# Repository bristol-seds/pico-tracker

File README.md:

bristol-seds.github.io/pico-tracker
======================
Available at http://bristol-seds.github.io/pico-tracker.

## Running the server for local testing

You need Jekyll installed:

    $ sudo gem install jekyll RedCloth

Start Jekyll:

    $ jekyll serve --watch

Note that changes to `_config.yml` may require restarting the server.

#Items from the main site, may not work here:

## Adding photo carousels

First put all photos in the `asset_path` directory for a post. Then list all in the front-matter like so:

    photos:
      - url: photo1.jpg
      - url: photo2.jpg
      - url: photo3.jpg

Then simply add {% raw %}`{% include carousel.html %}`{% raw %} where you want the carousel.

## Adding Javascript to posts

Make sure your post has an `asset_path` key-value pair.

### Google Maps

Add a new key, `maps:`, with a list of `url:` key-value pairs as its value, each having
a script containing a Google Maps generator as its value, e.g.:

    maps:
      - url: map1.js
      - url: map2.js

The scripts should be placed in the `asset_path` directory.
For each map, insert a `<div>` tag into the post, with a unique ID referenced by the map generator script.
**TO-DO**: Google Maps KML files must be hosted publicly. Find a way to automatically insert the KML file's fully-qualified url into a map script. Currently I'm just hosting them from http://samhatfield.co.uk

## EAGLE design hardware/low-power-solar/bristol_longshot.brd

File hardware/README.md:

#### Hardware Revisions

Most hardware that has been built has a version number

|Version|Description|Exists/Existed|Flights used on
|----|----|----|----
|v0.96.0|Original AAA Battery. Flown with modifications to connect tcxo to mcu.|x|UBSEDS3-8?+UBSEDS12
|v0.981.0|Solar Power SPV1040. Flown with modifications simplify power circuit.|x|UBSEDS9
|v0.981.1|Minor fixes|
|v0.982.0|AAA Battery. Never fully populated, used for lab testing.|x|
|v0.982.1|Minor fixes|
|v0.984.0|First attempt at internal balloon board|
|v0.985.0|Solar Power/Primary AAA Lithium|x|UBSEDS10-11
|v0.985.1|Added DNP/0Ω between solar and MPPT set for use when only a battery is connected|
|v0.985.2|BMP180 -> MS5607 Pressure / Temperature Sensor|
|v0.985.3|Smaller holes for external thermistor|
|v0.986.0|Low Power with side mounting GPS chip antenna|
|v0.986.1|Low Power. Add 10k i2c pull ups|
|v0.986.1|Low Power. Rearranged matching network|
|v0.986.3|Low Power. Added L0'-C0' tank in paralell. Might work, should test|
|v0.986.4|Low Power. Added LIS2D accelerometer. Optional|
|v0.986.5|Low Power. Added TS3006 low power lf clock|
|v0.986.6|Low Power. Added LDO for GPS, LF TCXO for GPS|
|v0.986.7|Low Power. Changed low power lf clock, added vreg on breakout for optional power testing|
|v0.986.8|Low Power. Changed memory pads, GPS LDO and specified SAMD20E18A-MN with more flash and higher grade packaging|x|
|v0.986.9|Low Power. 80x80mm Breakout|
|v0.987.0|Low Power. Added 32kHz TCXO RC filters, replaced GPS LDO with MOSFET, remove IMU, vreg on b/out, update SE880 footprint, Watchdog, Radio, filter design
|v0.987.1|Low Power. Switch LF Clock to XOSC32K pin from GCLK_IO[0]. Allows feed to any GCLK. Bit-bang i2c instead|
|v0.987.2|Low Power. Adjusted 100µF cap from 1210 to 1206|x|
|v0.987.3|Low Power. Added pull-down on WDI

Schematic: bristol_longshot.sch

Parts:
A1: 1575AT43A40
C0, C2: 15pF; _0402
C1, C3: 8.2pF; _0402
C4, C48: DNP; _0402
C5: 5.1pF; _0402
C6: 2.7pF; _0402
C7, C13, C14, C15, C16, C17, C18, C20, C21, C34, C46, C47, C49, C51: 100nF; _0402
C8, C9, C10: 100pF; _0402
C11, C30: 4.7µF; _0402
C12, C39, C40, C41, C42, C44, C45: 10nF; _0402
C19: 18nF; _0402
C22, C27, C33: 10µF; C0603K
C23, C24, C26, C35, C52: 1µF; _0402
C25, C28: 2.2µF; _0402
C29, C32: 100µF; C1206K
C31: 47nF; _0402
C36, C37: 56pF; _0402
C38: 39pF; _0402
C43: 27pF; _0402
C50: 10nF; _0805
D1, D2, D3, D4, D5: RB161M
D6: MBR0520LT1G; SOD123W
DZ1: 5V6, 500mW; SOD-323
FB1, FB2: FERRITE_0402; _0402
FB3: FERRITE_0603; _0603
JP1: BATTERY_TERMINAL; 1X02_LOCK
JP2: SOLAR_TERMINAL; 1X02_LOCK
JP3: M02LOCK; 1X02_LOCK
JTAG1: JTAG-CORTEXM3SMT; 2X05_1.27MM_SMT
L0, L6, L7: 56nH; _0402@2
L1: XFL4030-4.7µH; XFL4020
L2: 2.2µH; 1007
L3: 110nH; _0805MP
L4, L5, L11: 18nH; _0402@2
L8: EPL2010-680nH; EPL2010
L9, L10: 33nH; _0603MP
L12: 0Ω; _0402@2
LC: 470nH; _0402@2
LED1, LED2: GREEN; CHIPLED_0603
Q1, Q2: NX2301P; SOT23
Q3, Q4: BSS84; SOT23
Q5: PBSS4130; SOT1118
Q6: PD84001; SOT-89
R1, R2, R3, R4, R7, R8, R24, R27, R29, R30, R33: 10kΩ; _0402
R5: 20kΩ; _0402
R6, R9, R10, R11, R12, R13: 100kΩ; _0402
R14: 75kΩ; _0402
R15, R16, R17: 1MΩ; _0402
R18: 4.7kΩ; _0402
R19, R22, R31, R32: 1kΩ; _0402
R20, R21: 22Ω; _0603MP
R23: 4.7Ω; _0402
R25, R26: 33kΩ; _0402
R28: 330Ω; _0402
U1: SAM_D20E; QFN32_5MM
U2: SI4461; QFN20
U3: SE880
U4: SST25WF040BT-40I/NP; USON-8
U5: TG-5006CJ; TC-5006CJ
U6: TPS73118DBVT; SOT95P280X145-5N
U7: ADM6823WYRJZ; SOT23-5
U8: SN74LVC1G32DCKR; SOT65P210X110-5N
U9: TPS62243; S-PWSON-N6
U10, U11: SIT1552
U12: LTC4070EMS8EPBF; SOP65P490X110-9N
U13: ADP1614ACPZ-1.3-R7; DFN50P300X300X80-11N
U14, U15: TPS71533DCKR; SOT65P210X110-5N
U16, U17, U18: 74LVC1G04GW; SOT65P210X110-5N
U19: AS213-92; SOT-6
U20: SKY13373

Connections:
1.8V: C10.1, C15.1, C17.1, C21.1, C32.1, C33.1, FB1.2, FB2.2, FB3.2, JTAG1.1, L2.2, LED1.A, R4.2, R12.2, R31.2, R32.2, U1.9 (VDD_ANA), U1.30 (VDD), U4.7 (!HOLD), U4.8 (VDD), U7.3 (!MR), U7.5 (VDD), U8.5 (VCC), U9.3 (FB), U10.3 (VCC), U17.5 (VCC), U18.5 (VCC)
1.8V_EN: JP3.1, R30.2, U9.4 (EN)
2M_FILTER_1: C36.1, C39.2, L9.1
2M_FILTER_2: C37.1, L9.2, L10.1
2M_FILTER_3: C38.1, C45.1, L10.2
7.5V: C27.1, C29.1, C51.1, D6.P$2 (2), L3.2, R9.2, U14.4 (IN)
!GPS_EN: Q1.1 (G), R15.1, U1.2 (PA01)
!RESET: U1.26 (RESETN), U8.4 (Y)
AMPL_DRAIN: C39.1, L3.1, Q6.3 (D)
AMPL_GATE: L11.2, Q6.1 (G), R19.1
AMPL_IN: C41.2, C43.1, L11.1
AMPL_IN1: C41.1, U19.3 (J2)
AMPL_OUT: C45.2, U20.1 (J1)
ANT: C48.1, L12.2
ANT1: C4.1, C40.2, L12.1
BATTERY: C22.1, D3.ANODE (A), JP1.1, Q4.3 (D), R23.2, R25.2, U12.2 (NTC), U12.8 (VCC)
BATTERY_MOSFET_1: Q3.3 (D), Q4.2 (S)
BATTERY_SENSE: R24.2, R25.1, U1.5 (PA04)
BOOST_COMP: R18.2, U13.1 (COMP)
BOOST_COMP_1: C19.1, R18.1
BOOST_CURRENTLIMIT: R14.2, U13.9 (CLRES)
BOOST_FB: R5.2, R9.1, U13.2 (FB)
BOOST_SOFTSTART: C31.1, U13.10 (SS)
BOOST_SUPPLY: C30.1, L1.1, Q2.3 (D), U13.3 (EN), U13.8 (VIN)
BOOST_SUPPLY_CTRL_B: Q5.P2 (B), R29.2
BOOST_SUPPLY_CTRL_C: Q2.1 (G), Q5.P3 (C), Q5.P8 (C), R10.2
BOOST_SW: D6.P$1 (1), L1.2, U13.6 (SW_2), U13.7 (SW)
BUCK_SW: L2.1, U9.1 (SW)
BYPASS: C42.2, U20.3 (J3)
BYPASS1: C42.1, U19.1 (J3)
CHG_CTRL: R33.1, U1.25 (PA27)
CHG_CTRL_B: Q5.P5 (B), R33.2
CHG_CTRL_C: Q3.1 (G), Q4.1 (G), Q5.P6 (C), Q5.P7 (C), R6.2
CHG_LED: LED2.A, R28.1
EXT!RESET: JTAG1.10, R1.2, U8.1 (A)
EXT_THERMISTOR_SENSE: R11.2, U1.3 (PA02)
FILTER1: C3.1, L0.1, L4.2
FILTER2: C2.1, L4.1, L5.2
GIMO: U1.7 (PA06), U3.34 (RX)
GND: C1.2, C2.2, C3.2, C4.2, C5.2, C7.2, C8.2, C9.2, C10.2, C11.2, C12.2, C15.2, C16.2, C17.2, C19.2, C20.2, C21.2, C22.2, C23.2, C24.2, C25.2, C26.2, C27.2, C28.2, C29.2, C30.2, C31.2, C32.2, C33.2, C34.2, C35.2, C36.2, C37.2, C38.2, C43.2, C46.1, C47.1, C48.2, C49.2, C51.2, C52.2, DZ1.A, JP1.2, JP2.2, JP3.2, JTAG1.3, JTAG1.5, LED2.C, Q5.P1 (E), Q5.P4 (E), Q6.2 (S), Q6.2.1 (S), R1.1, R2.1, R3.1, R5.1, R11.1, R13.1, R14.1, R16.1, R17.1, R22.1, R24.1, R27.1, U1.10 (GND1), U1.28 (GND2), U1.33 (GND), U2.5 (NC/GND), U2.18 (GND2), U2.PAD (GND), U3.1 (GND1), U3.5 (GND2), U3.18 (GND3), U3.20 (GND4), U3.23 (GND5), U3.24 (GND6), U3.25 (GND7), U3.26 (GND8), U3.28 (GND9), U3.29 (GND10), U4.4 (VSS), U5.2 (GND), U6.2 (GND), U7.2 (GND), U8.3 (GND), U9.2 (MODE), U9.6 (GND), U9.PAD (GND2), U10.1 (GND), U10.4 (GND1), U11.1 (GND), U11.4 (GND1), U12.3 (ADJ), U12.5 (GND), U12.9 (EP), U13.4 (GND_2), U13.5 (GND), U13.11 (EP), U14.2 (GND), U15.2 (GND), U16.3 (GND), U17.3 (GND), U18.3 (GND), U19.2 (GND), U20.2 (GND), U20.7 (GND1), U20.8 (GND2), U20.10 (GND3), U20.12 (GND4), U20.PAD
GOMI: U1.8 (PA07), U3.33 (TX)
GPS_ANT: A1.1 (ANT), U3.27 (RF_IN)
GPS_VDD: FB3.1, Q1.2 (S), R15.2
GPS_VDD_SWITCHED: C7.1, C9.1, C28.1, Q1.3 (D), U3.8 (VKA), U3.9 (VDD), U11.3 (VCC)
HBO: R28.2, U12.4 (HBO)
LED1: LED1.C, U1.16 (PA15)
LF_CLOCK: R7.1, U1.1 (PA00)
LF_CLOCK_OUT: R7.2, U10.2 (OUT)
LIION_CAP: C49.1, D4.CATHODE (C), D5.ANODE (A)
LIION_CAP_FEED: D4.ANODE (A), R23.1
MEM_CSN: U1.13 (PA10), U4.1 (!CE)
MEM_MISO: U1.14 (PA11), U4.2 (SO/SIO1)
MEM_MOSI: U1.11 (PA08), U4.5 (SI/SIO0)
MEM_SCK: U1.12 (PA09), U4.6 (SCK)
MEM_WPN: U4.3 (!WP)
NTCBIAS: U12.1 (NTCBIAS)
RADIO_VDD: C8.1, C20.1, C25.1, C34.1, FB1.1, LC.2, U2.6 (VDD), U2.8 (VDD2), U16.5 (VCC)
RADIO_XIN: C13.2, U2.17 (XIN)
RF_SW_V2: C47.2, U16.4 (Y), U19.6 (V2)
RF_TANK: C0.1, L0.2
RF_TCXO_REG_EN: U1.17 (PA16), U6.3 (EN)
RTC_XI: R8.1, U3.12 (RTC_XI)
RTC_XO: U3.13 (RTC_XO)
RX: C6.1, C50.1, L7.1
RXN: C5.1, L6.1, L7.2, U2.2 (RXP)
RXP: C6.2, L6.2, U2.3 (RXN)
RX_1: C50.2, U20.9 (J2)
SAM_XOSC: C18.1, R12.1, R13.2, U1.15 (PA14)
SE800_LF_OUT: R8.2, U11.2 (OUT)
SE_GPIO0: R2.2, U3.17 (GPIO0)
SE_GPIO1: R3.2, U3.16 (GPIO1)
SE_MODE_PULL: R4.1, U3.31 (CTS_SPI)
SE_ON_OFF: U1.6 (PA05), U3.3 (ON_OFF)
SE_TCXO_CLK: C14.1, U3.21 (TCXO_CLK)
SE_VBB: L8.1, U3.6 (VBB_I)
SE_VREG: L8.2, U3.7 (VREG_O)
SI_GPIO0: C46.2, R22.2, R29.1, U2.9 (GPIO0), U16.2 (A), U19.4 (V1)
SI_GPIO1: U1.24 (PA25), U2.10 (GPIO1)
SI_GPIO2: R31.1, U2.19 (GPIO2), U17.2 (A)
SI_GPIO3: R32.1, U2.20 (GPIO3), U18.2 (A)
SI_MISO: U1.21 (PA22), U2.13 (SDO)
SI_MOSI: U1.20 (PA19), U2.14 (SDI)
SI_NIRQ: U1.23 (PA24), U2.11 (NIRQ)
SI_NSEL: U1.19 (PA18), U2.15 (NSEL)
SI_SCLK: U1.22 (PA23), U2.12 (SCLK)
SI_SDN: U1.18 (PA17), U2.1 (SDN)
SI_TX: C0.2, LC.1, U2.4 (TX)
SKY_OUT: C40.1, U20.11 (RFC)
SKY_V1: R20.1, U20.4 (V1)
SKY_V1_1: R20.2, U17.4 (Y)
SKY_V2: R21.1, U20.5 (V2)
SKY_V2_1: R21.2, U18.4 (Y)
SOLAR1: D1.ANODE (A)
SOLAR2: D2.ANODE (A)
SWDCLK: JTAG1.4, U1.31 (PA30/SWCLK)
SWDIO: JTAG1.2, U1.32 (PA31/SWDIO)
TCXO_OUT: C13.1, C14.2, C18.2, U5.3 (OUT)
TCXO_REG_IN: C23.1, FB2.1, U6.1 (IN)
TCXO_REG_NR: C12.1, U6.4 (NR/FB)
TCXO_VDD: C24.1, U5.4 (VCC), U6.5 (OUT)
TIMEPULSE: U3.4 (TM)
TX: C1.1, C44.1, L5.1
TX_1: C44.2, U19.5 (J1)
VDD_CORE: C16.1, U1.29 (VDD_CORE)
V_BUS: C11.1, C52.1, D1.CATHODE (C), D2.CATHODE (C), D3.CATHODE (C), D5.CATHODE (C), DZ1.C, JP2.1, Q2.2 (S), Q3.2 (S), R6.1, R10.1, R26.2, R30.1, U9.5 (VIN), U15.4 (IN)
V_BUS_SENSE: R26.1, R27.2, U1.4 (PA03)
V_GG: C26.1, R19.2, U14.5 (OUT)
V_SKY: C35.1, U15.5 (OUT), U20.6 (VDD)
WDI: R17.2, U1.27 (PA28), U7.4 (WDI)
WDI!RESET: R16.2, U7.1 (!RESET), U8.2 (B)

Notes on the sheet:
ARM Cortex M0+: Atmel SAM D20E
(SERCOM3)
(SWD)
(EXTINT[12])
(DO: PAD3, SCK: PAD1)
(DOPO: 0x2)
(SERCOM2)
(DO: PAD0, SCK: PAD1, DOPO: 0x0)
(SERCOM0)
(TX: PAD2, TXPO: 0x1)
SST25WF04 4 MBit SPI Flash
Si4468 Transciever
Tuned for 434MHz
Radio
(0.8V p-p min)
(AIN[4])
Microcontroller
Set UART 115200 OSP
Set UART
(AIN[0])
SiT1552 Low frequency clock
Bypass Capacitors near SE880 main feed
Startup within 300ms
C15 in close proximity
MOSFET included to cycle GPS power as required
V_GSth = -1.1V @ Id = 0.1A
R_DSon = 0.2Ω @ V_GS = -1.8V, Id = 0.1A
approx. 20mV dropout
Input C < 15pF
Battery Voltage
Use ADM6823WYRJZ
Vth = 1.62-1.71V t_RP = 140-280ms t_WD = 1.12-2.4s
t_WD is 0.93x nominal at -40ºC
XOSC32K_IN
Icc = 5µA nominal at 1.8V
Icc = 10µA max
Pull-down to ensure watchdog bites if WDI left floating pre-init
Input Voltage: 2 - 6V
Enable: Vil = 0.4V, Vih=1V
Undervoltage Lockout: 1.85V typ

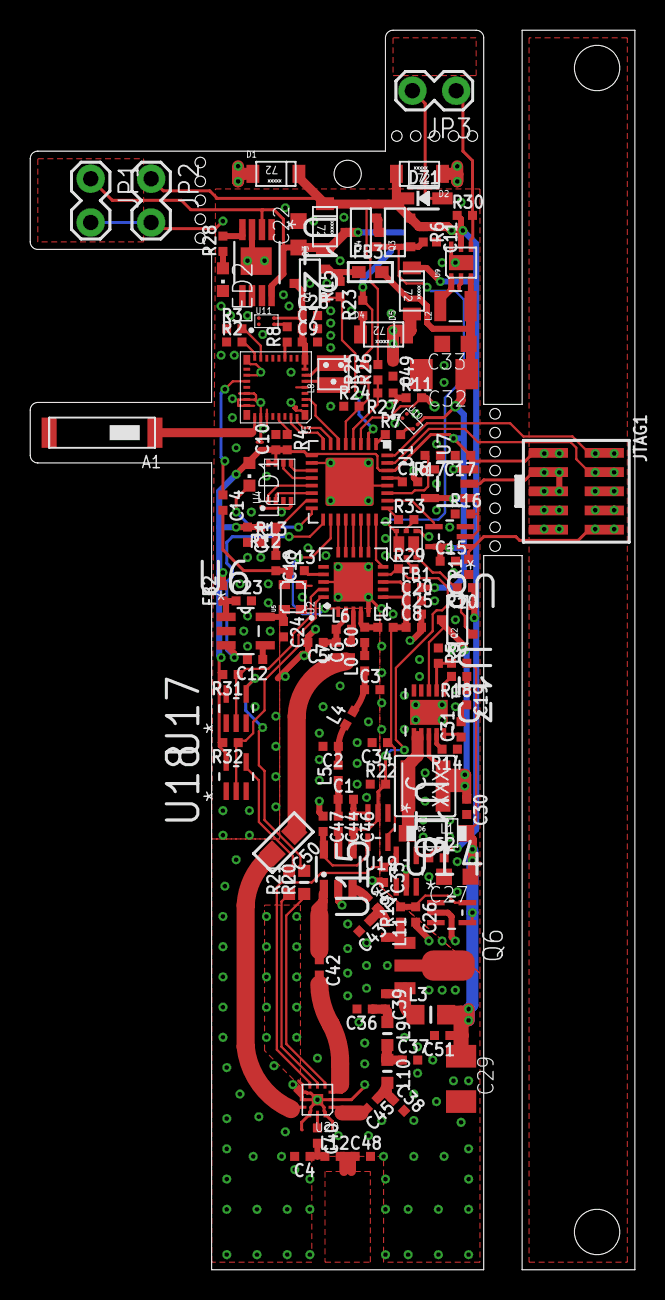
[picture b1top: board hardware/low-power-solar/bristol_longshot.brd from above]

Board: 2 copper layers, 40.0 x 82.0 mm, 143 parts (0 on the bottom side), 104 nets.

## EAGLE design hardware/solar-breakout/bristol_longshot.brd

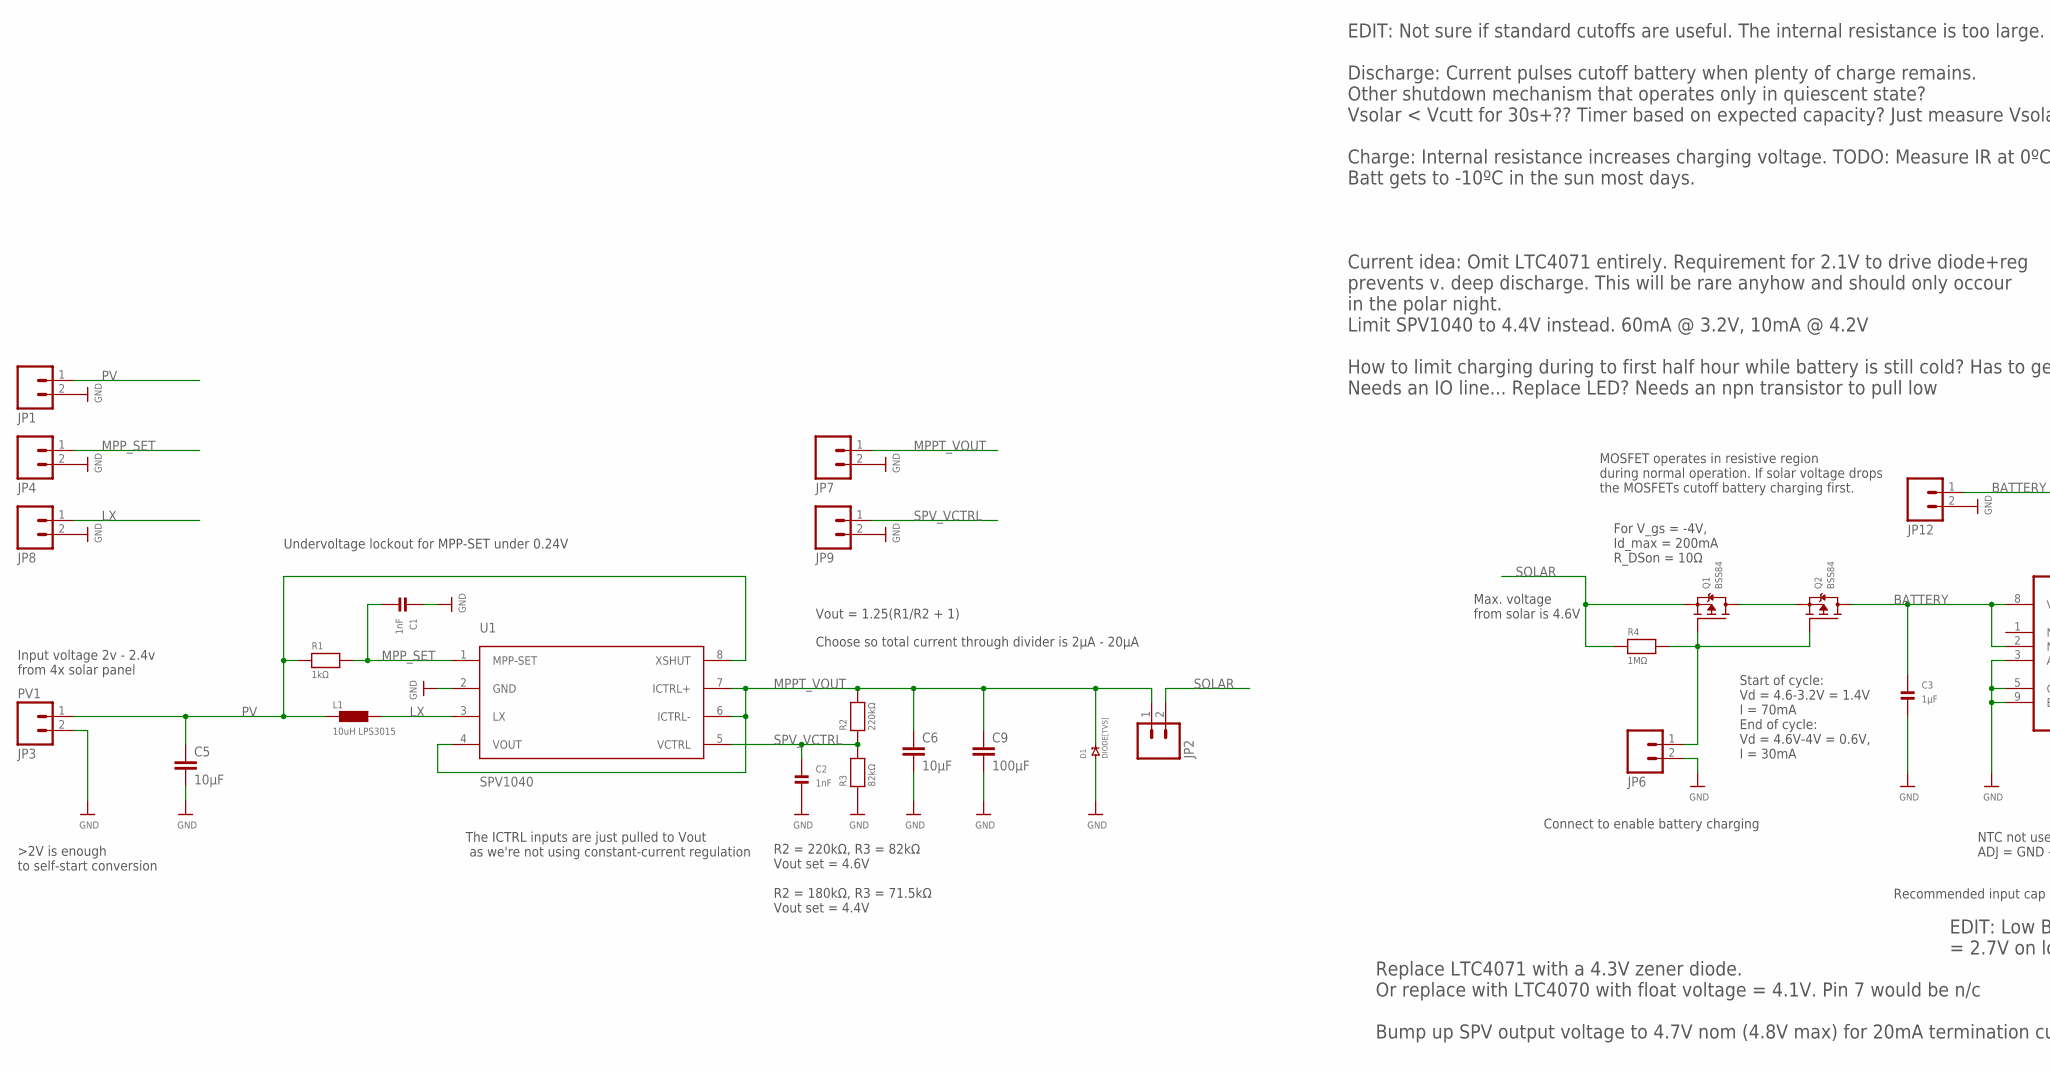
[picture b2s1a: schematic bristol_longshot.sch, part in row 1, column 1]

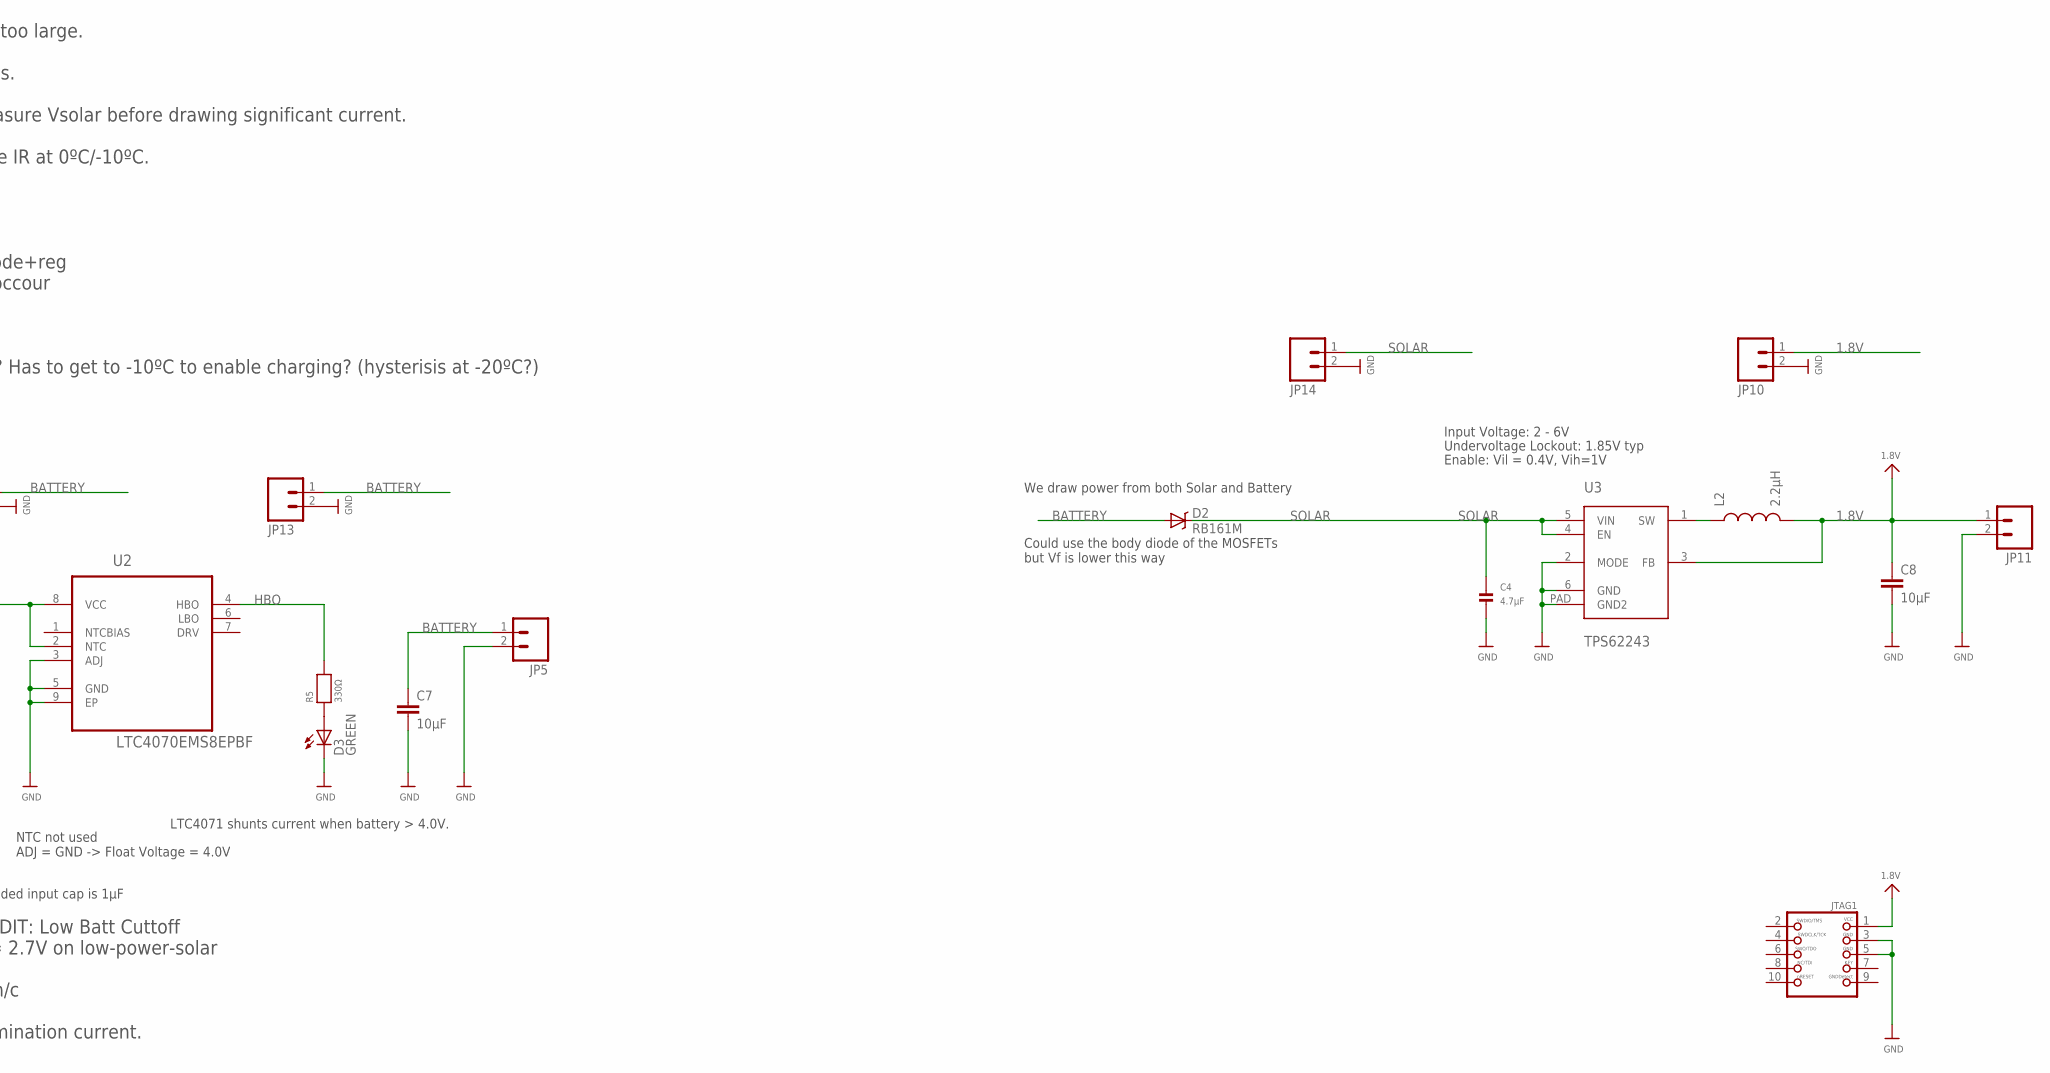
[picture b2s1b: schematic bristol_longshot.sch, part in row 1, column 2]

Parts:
C1, C2: 1nF; _0402@1
C3: 1µF; _0402@1
C4: 4.7µF; _0402@1
C5, C6, C7, C8: 10µF; C0603K
C9: 100µF; C1206K
D1: DIODE[TVS]; SOD123W
D2: RB161M
D3: GREEN; CHIPLED_0603
JP1, JP2, JP4, JP6, JP7, JP8, JP9, JP10, JP12, JP13, JP14: M02LOCK; 1X02_LOCK
JP3: PV1; SCREWTERMINAL-3.5MM-2_LOCK
JP5, JP11: M023.5MM_LOCK; SCREWTERMINAL-3.5MM-2_LOCK
JTAG1: JTAG-CORTEXM3SMT; 2X05_1.27MM_SMT
L1: 10uH LPS3015; LPS3015
L2: 2.2µH; 1007
Q1, Q2: BSS84; SOT23
R1: 1kΩ; _0402
R2: 220kΩ; _0402
R3: 82kΩ; _0402
R4: 1MΩ; _0402
R5: 330Ω; _0402
U1: SPV1040; TSSOP8
U2: LTC4070EMS8EPBF; SOP65P490X110-9N
U3: TPS62243; S-PWSON-N6

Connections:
1.8V: C8.1, JP10.1, JP11.1, JTAG1.1, L2.2, U3.3 (FB)
BATTERY: C3.1, C7.1, D2.ANODE (A), JP5.1, JP12.1, JP13.1, Q2.3 (D), U2.2 (NTC), U2.8 (VCC)
BATTERY_MOSFET_1: Q1.3 (D), Q2.2 (S)
BATT_MOSFET_CTRL: JP6.1, Q1.1 (G), Q2.1 (G), R4.2
CHG_LED: D3.A, R5.1
GND: C1.1, C2.2, C3.2, C4.2, C5.2, C6.2, C7.2, C8.2, C9.2, D1.P$1 (1), D3.C, JP1.2, JP3.2, JP4.2, JP5.2, JP6.2, JP7.2, JP8.2, JP9.2, JP10.2, JP11.2, JP12.2, JP13.2, JP14.2, JTAG1.3, JTAG1.5, R3.1, U1.2 (GND), U2.3 (ADJ), U2.5 (GND), U2.9 (EP), U3.2 (MODE), U3.6 (GND), U3.PAD (GND2)
HBO: R5.2, U2.4 (HBO)
LX: JP8.1, L1.2_1 (2), L1.2_2 (2), L1.2_3 (2), L1.2_4 (2), L1.2_5 (2), L1.2_6 (2), L1.2_7 (2), L1.2_8 (2), L1.2_9 (2), U1.3 (LX)
MPPT_VOUT: C6.1, C9.1, D1.P$2 (2), JP2.1, JP7.1, R2.2, U1.4 (VOUT), U1.6 (ICTRL-), U1.7 (ICTRL+)
MPP_SET: C1.2, JP4.1, R1.2, U1.1 (MPP-SET)
unnamed: L2.1, U3.1 (SW)
NTCBIAS: U2.1 (NTCBIAS)
PV: C5.1, JP1.1, JP3.1, L1.1_1 (1), L1.1_2 (1), L1.1_3 (1), L1.1_4 (1), L1.1_5 (1), L1.1_6 (1), L1.1_7 (1), L1.1_8 (1), L1.1_9 (1), R1.1, U1.8 (XSHUT)
SOLAR: C4.1, D2.CATHODE (C), JP2.2, JP14.1, Q1.2 (S), R4.1, U3.4 (EN), U3.5 (VIN)
SPV_VCTRL: C2.1, JP9.1, R2.1, R3.2, U1.5 (VCTRL)

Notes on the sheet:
Input Voltage: 2 - 6V
Enable: Vil = 0.4V, Vih=1V
Undervoltage Lockout: 1.85V typ
Undervoltage lockout for MPP-SET under 0.24V
The ICTRL inputs are just pulled to Vout as we're not using constant-current regulation
Recommended input cap is 1µF
Vout = 1.25(R1/R2 + 1)
Choose so total current through divider is 2µA - 20µA
Input voltage 2v - 2.4v from 4x solar panel
We draw power from both Solar and Battery
R2 = 220kΩ, R3 = 82kΩ Vout set = 4.6V R2 = 180kΩ, R3 = 71.5kΩ Vout set = 4.4V
NTC not used ADJ = GND -> Float Voltage = 4.0V
LTC4071 shunts current when battery > 4.0V.
Start of cycle: Vd = 4.6-3.2V = 1.4V I = 70mA End of cycle: Vd = 4.6V-4V = 0.6V, I = 30mA
Max. voltage from solar is 4.6V
For V_gs = -4V, Id_max = 200mA R_DSon = 10Ω
MOSFET operates in resistive region during normal operation. If solar voltage drops the MOSFETs cutoff battery charging first.
Connect to enable battery charging
Could use the body diode of the MOSFETs but Vf is lower this way
EDIT: Not sure if standard cutoffs are useful. The internal resistance is too large. Discharge: Current pulses cutoff battery when plenty of charge remains. Other shutdown mechanism that operates only in quiescent state? Vsolar < Vcutt for 30s+?? Timer based on expected capacity? Just measure Vsola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
EDIT: Low Batt Cuttoff = 2.7V on low-power-solar
Current idea: Omit LTC4071 entirely. Requirement for 2.1V to drive diode+reg prevents v. deep discharge. This will be rare anyhow and should only occour in the polar night. Limit SPV1040 to 4.4V instead. 60mA @ 3.2V, 10mA @ 4.2V How to limit charging during to first half hour while battery is still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
Replace LTC4071 with a 4.3V zener diode. Or replace with LTC4070 with float voltage = 4.1V. Pin 7 would be n/c Bump up SPV output voltage to 4.7V nom (4.8V max) for 20mA termination current.

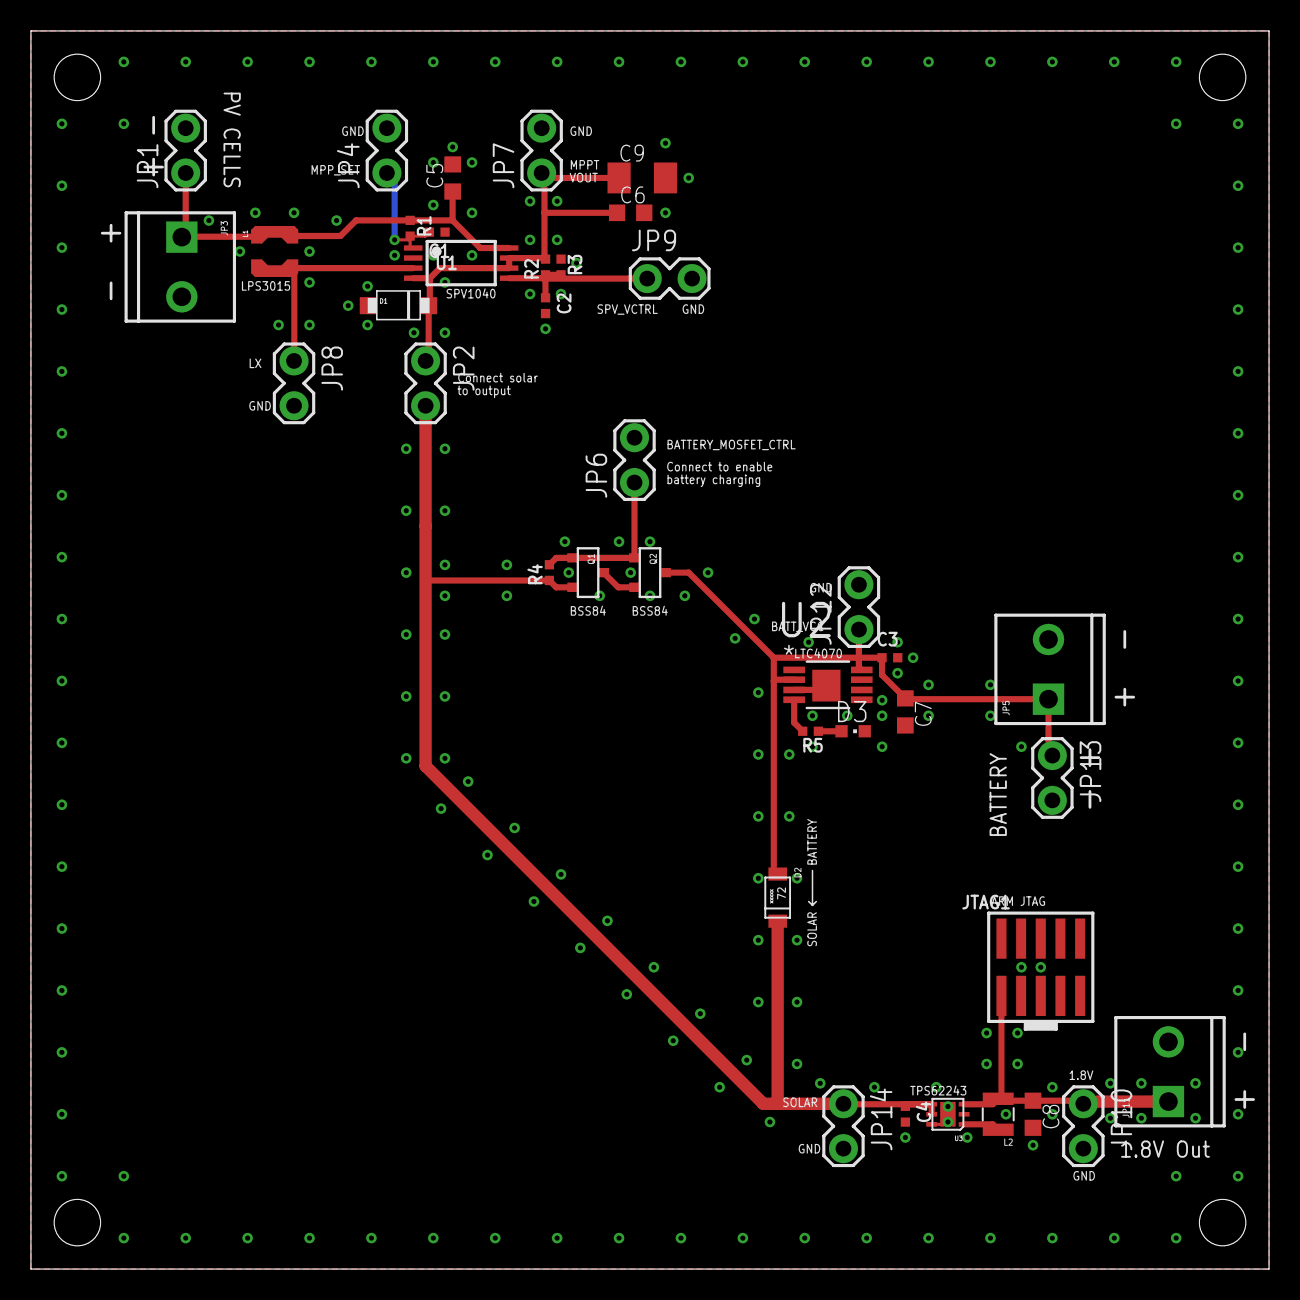
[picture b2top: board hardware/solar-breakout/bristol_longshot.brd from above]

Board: 2 copper layers, 80.0 x 80.0 mm, 39 parts (0 on the bottom side), 14 nets.

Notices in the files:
parts and their libraries:
SparkFun: Licensing: CC v3.0 Share-Alike You are welcome to use this library for commercial purposes.
microbuilder_v3: This work is placed in the public domain, and may be freely used for commercial and non-commercial work with the following conditions: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
